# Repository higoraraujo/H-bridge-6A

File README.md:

# 6A H-Bridge Motor Control with Arduino

This project demonstrates how to control a DC motor using a 6A H-bridge and an Arduino, allowing direction reversal and speed control through PWM.

## Requirements
- Arduino (Uno, Nano or similar)
- 6A H-bridge driver
- Compatible DC motor
- Power supply suitable for the motor
- Jumper wires and prototyping components

## Connections

| Component | Arduino Pin | Description |
|-----------|-------------|-------------|
| IN1       | 8           | Direction input 1 |
| IN2       | 9           | Direction input 2 |
| ENA (PWM) | 10          | Motor enable / Speed control |
| Vcc       | 5V          | Logic supply |
| GND       | GND         | Ground reference |

Motor power must be connected directly to the H-bridge, respecting the motor's current rating.

## Usage
1. Connect the components according to the table above.
2. Upload `Code/HBridgeControl.ino` to your Arduino.
3. (Optional) Open the Serial Monitor for debugging.
4. The motor will alternate between forward and reverse rotations with programmed pauses.

### Advanced control

For more flexibility, try `Code/Code.ino`. This sketch configures Timer1 for a
20 kHz PWM frequency and exposes helper functions to:

- Smoothly ramp speed in either direction
- Change PWM frequency at runtime
- Drive the motor using only two hardware PWM pins (OC1A/OC1B)

Use this version when you need finer control over switching frequency or wish
to experiment with acceleration profiles.

## Safety
- Use appropriate fuses to protect against short circuits.
- Avoid touching the H-bridge or motor while powered.
- Ensure the power supply can handle the motor's current draw.

## Flowchart
```mermaid
flowchart TD
    A[Start] --> B[Configure pins]
    B --> C[Spin forward]
    C --> D[Delay 3s]
    D --> E[Stop motor]
    E --> F[Delay 1s]
    F --> G[Spin backward]
    G --> H[Delay 3s]
    H --> I[Stop motor]
    I --> J[Delay 1s]
    J --> C
```

## License
This project is licensed under the MIT License.

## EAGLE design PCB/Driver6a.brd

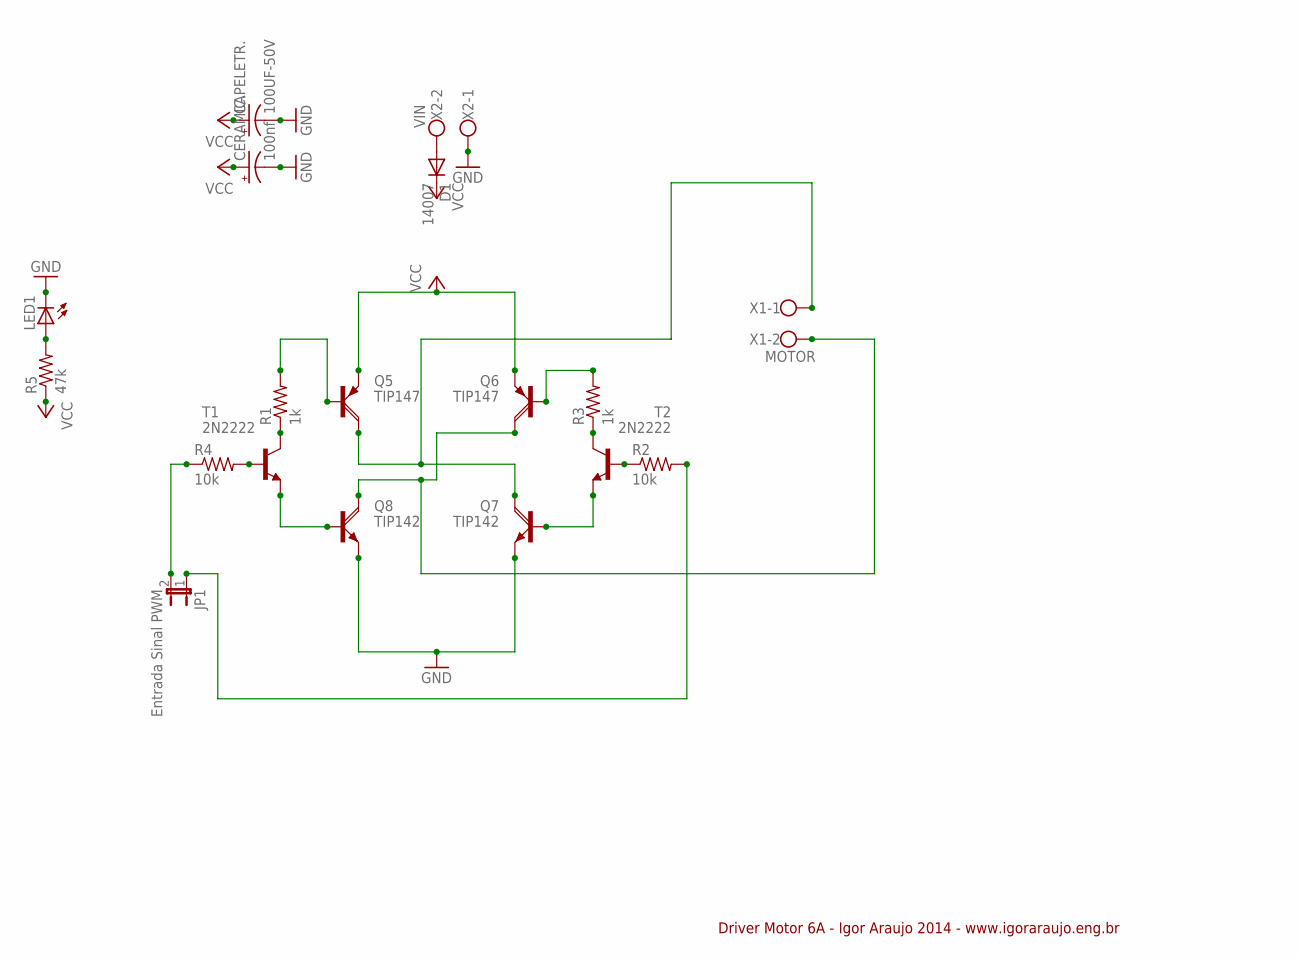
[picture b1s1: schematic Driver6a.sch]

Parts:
CAPELETR.: 100UF-50V; E3,5-8
CERAMIC.: 100nf; E3,5-8
D1: 14007; DO35-7
JP1: Entrada Sinal PWM; JP1
LED1: LED3MM
Q5, Q6: TIP147; TO220AH
Q7, Q8: TIP142; TO220AH
R1, R3: 1k; 0207/10
R2, R4: 10k; 0207/10
R5: 47k; 0207/10
T1, T2: 2N2222; TO18
X1: MOTOR; W237-132
X2: VIN; W237-132

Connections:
GND: CAPELETR..-, CERAMIC..-, LED1.K (C), Q7.E, Q8.E, X2.1
unnamed: Q5.C, Q7.C, X1.1
unnamed: Q6.C, Q8.C, X1.2
unnamed: R1.1, T1.3 (C)
unnamed: Q5.B, R1.2
unnamed: Q8.B, T1.1 (E)
unnamed: R3.1, T2.3 (C)
unnamed: Q6.B, R3.2
unnamed: Q7.B, T2.1 (E)
unnamed: R2.1, T2.2 (B)
unnamed: R4.2, T1.2 (B)
unnamed: JP1.2, R4.1
unnamed: JP1.1, R2.2
unnamed: LED1.A, R5.2
unnamed: D1.A, X2.2
VCC: CAPELETR..+, CERAMIC..+, D1.C, Q5.E, Q6.E, R5.1

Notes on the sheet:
Driver Motor 6A - Igor Araujo 2014 - www.igoraraujo.eng.br

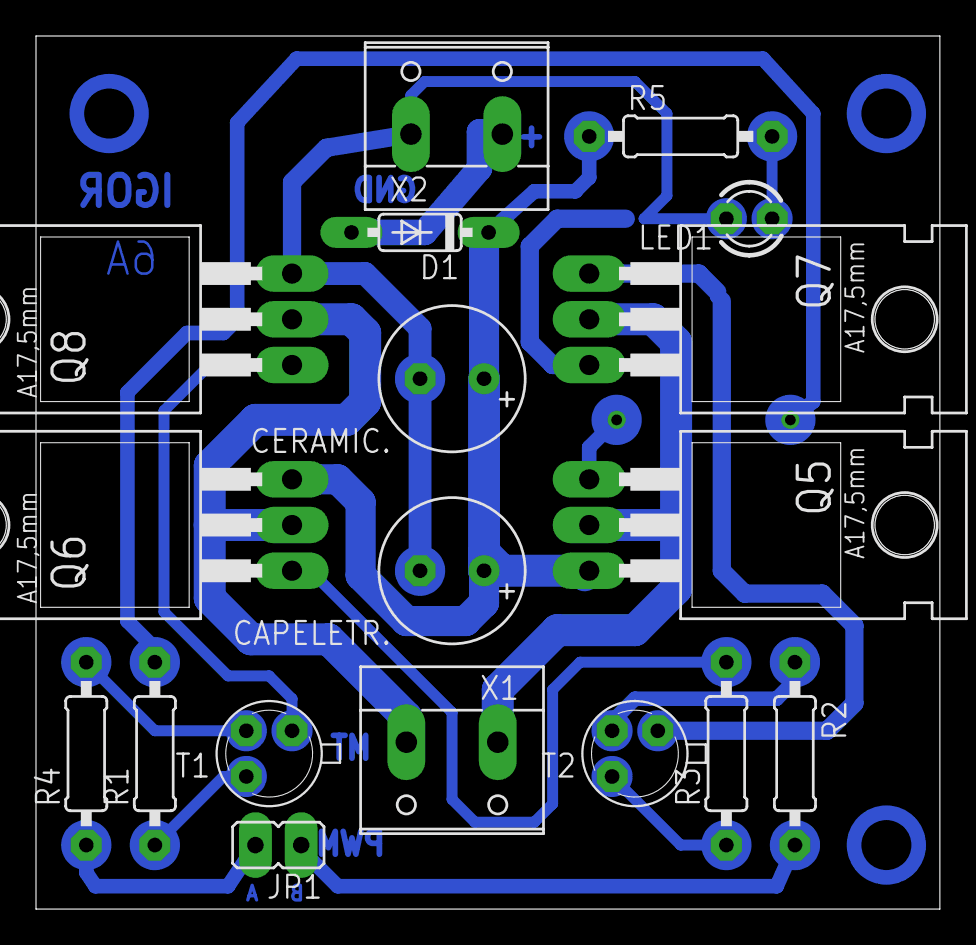
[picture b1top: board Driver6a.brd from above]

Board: 2 copper layers, 50.2 x 48.5 mm, 18 parts (0 on the bottom side), 16 nets.

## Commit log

2014-11-04 H-bridge - 6A
    Code - Controling one motor DC + H-bridge 6A + Arduino - by Igor
    Araujo 2014
    2x pins PWM for control.
2025-08-08 Constrain motor speed to valid PWM range
2025-08-08 Add English motor control example and documentation
2025-08-08 feat: add timer-based motor control with configurable pwm
